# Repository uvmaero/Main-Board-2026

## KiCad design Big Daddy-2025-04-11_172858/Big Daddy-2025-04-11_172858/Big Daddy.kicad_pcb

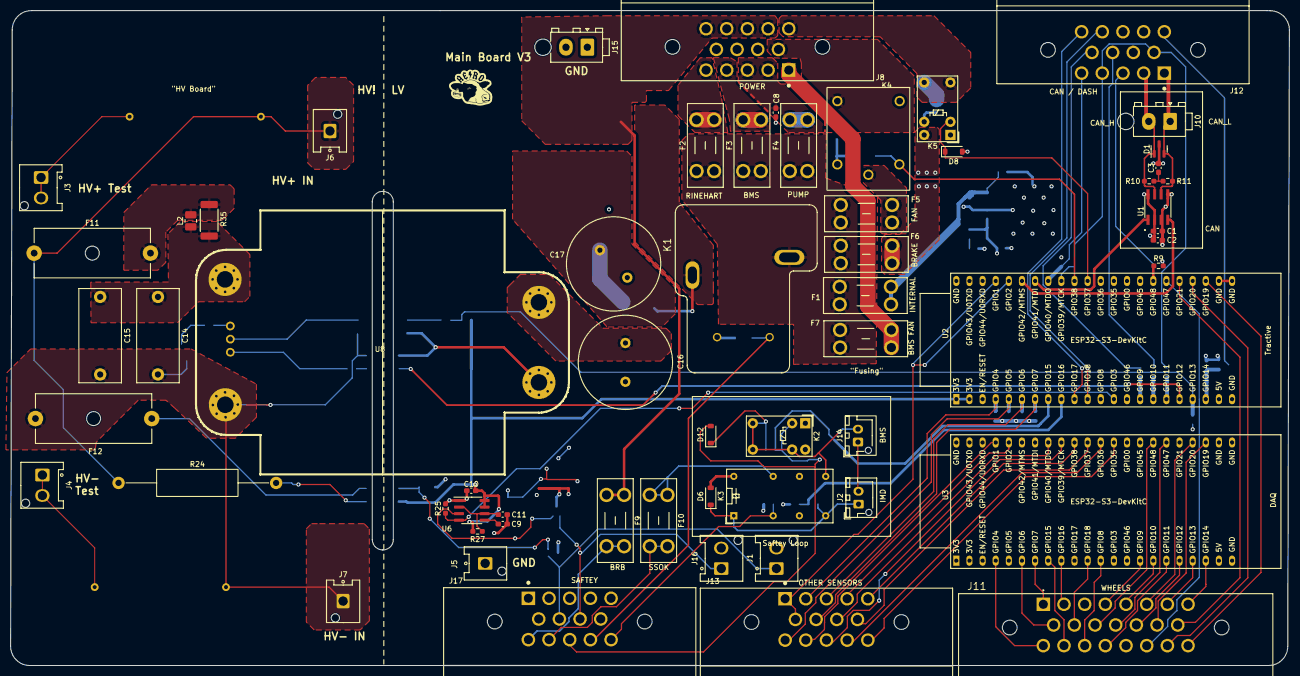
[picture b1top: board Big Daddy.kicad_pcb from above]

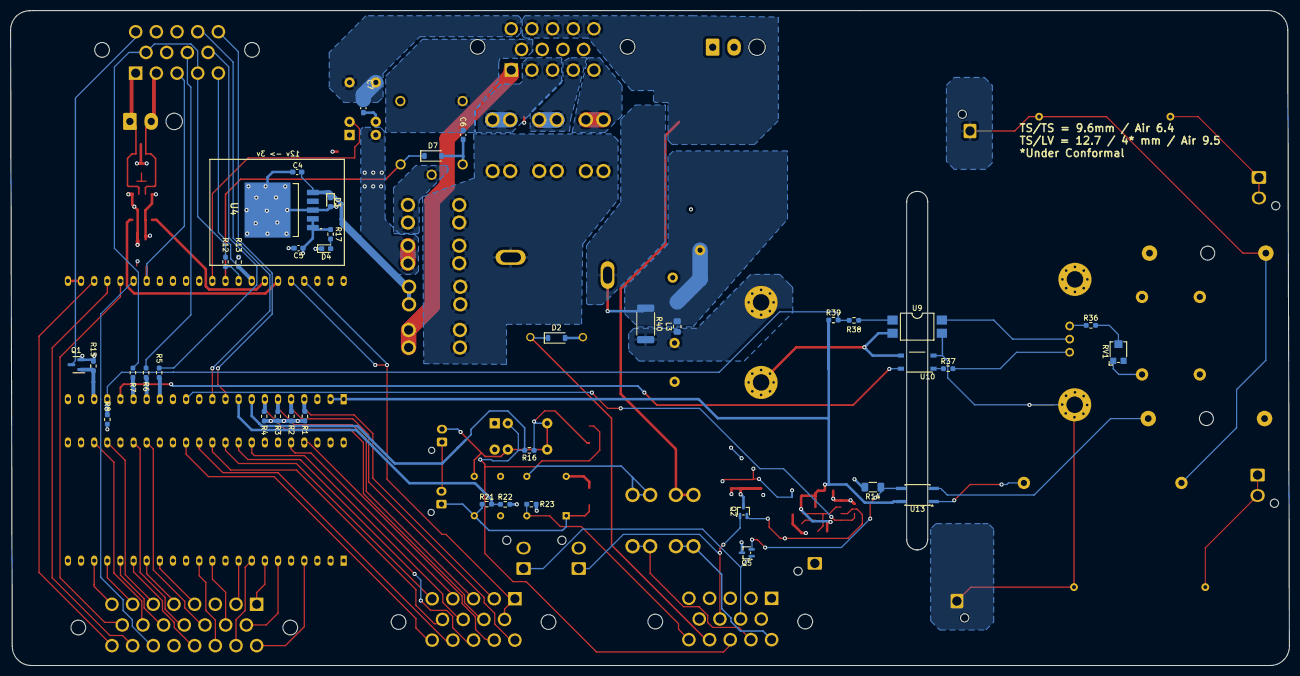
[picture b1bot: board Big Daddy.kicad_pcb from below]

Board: 4 copper layers, 247.3 x 126.6 mm, 101 parts (39 on the bottom side), 102 nets.

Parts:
C1, C2, C3, C9, C10: .1uF; C_0603_1608Metric_Pad1.08x0.95mm_HandSolder
C4, C6, C7, C8, C11: 10uF; C_0603_1608Metric_Pad1.08x0.95mm_HandSolder
C5: 22uF; C_0603_1608Metric_Pad1.08x0.95mm_HandSolder
C14, C15: 0.68uF; C_Rect_L18.0mm_W8.0mm_P15.00mm_FKS3_FKP3
C16, C17: 4700uF; C_Radial_D18.0mm_H35.5mm_P7.50mm
D1: DESD2CAN2SOQ-7; SOT-23
D2, D6, D7, D8, D12: 1N4148W; D_SOD-123
D3: TS4148C RZG; D_0603_1608Metric_Pad1.05x0.95mm_HandSolder
D4: LED; LED_0603_1608Metric_Pad1.05x0.95mm_HandSolder
F1, F4, F6, F7: 2A; Fuseholder_Blade_Mini_Keystone_3568
F2: 10A; Fuseholder_Blade_Mini_Keystone_3568
F3, F5: 5A; Fuseholder_Blade_Mini_Keystone_3568
F9, F10: 1A; Fuseholder_Blade_Mini_Keystone_3568
F11: 5A; Fuseholder_Cylinder-5x20mm_Schurter_0031_8201_Horizontal_Op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
F12: 1A; Fuseholder_Cylinder-5x20mm_Schurter_0031_8201_Horizontal_Op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
J1: TSSI_Grn I/O; Hirose_DF63R-2P-3.96DSA_1x02_P3.96mm_Vertical
J2: IMD Button; JST_XH_B2B-XH-AM_1x02_P2.50mm_Vertical
J3: HV+; Hirose_DF63R-2P-3.96DSA_1x02_P3.96mm_Vertical
J4: HV-; Hirose_DF63R-2P-3.96DSA_1x02_P3.96mm_Vertical
J5: GND; Hirose_DF63M-1P-3.96DSA_1x01_P3.96mm_Vertical
J6: HV+; Hirose_DF63M-1P-3.96DSA_1x01_P3.96mm_Vertical
J7: HV-; Hirose_DF63M-1P-3.96DSA_1x01_P3.96mm_Vertical
J8, J12, J13, J17: Conn_01x14; TE_1-776266-1_14pin_Horizontal
J10, J15: Conn_01x02; TE_MATE-N-LOK_1-770866-x_1x02_P4.14mm_Vertical
J11: Conn_01x23; TE_1-770669-1_23pin_Horizontal
J14: BMS Button; JST_XH_B2B-XH-AM_1x02_P2.50mm_Vertical
J16: TSSI_Red I/O; Hirose_DF63R-2P-3.96DSA_1x02_P3.96mm_Vertical
K1: T9VV1K15-12S; RELAY_T9VV1K15-12S
K2, K5: G5V-1; Relay_SPDT_Omron_G5V-1
K3: G5V-2; Relay_DPDT_Omron_G5V-2
K4: J107; J1071AS3VDC
L2: 1uH; L_1008_2520Metric_Pad1.43x2.20mm_HandSolder
L3: 0.15uH; L_0805_2012Metric_Pad1.15x1.40mm_HandSolder
Q1: 2N7002; SOT-23
Q2, Q5: RU1C002UN; SOT-323_SC-70
R1, R2, R3, R4, R8, R9, R13, R15, R23, R25: 10k; R_0603_1608Metric_Pad0.98x0.95mm_HandSolder
R5, R6, R7, R12, R17: 330; R_0603_1608Metric_Pad0.98x0.95mm_HandSolder
R10, R11: 60; R_0603_1608Metric_Pad0.98x0.95mm_HandSolder
R14: 2200; R_1206_3216Metric_Pad1.30x1.75mm_HandSolder
R16, R22: 2.2k; R_0603_1608Metric_Pad0.98x0.95mm_HandSolder
R21: 5.97k; R_0603_1608Metric_Pad0.98x0.95mm_HandSolder
R24: 300k; R_Axial_DIN0516_L15.5mm_D5.0mm_P30.48mm_Horizontal
R27: 24k; R_0603_1608Metric_Pad0.98x0.95mm_HandSolder
R32, R33: 20k; R_Axial_DIN0309_L9.0mm_D3.2mm_P5.08mm_Vertical
R35, R40: 1; R_2512_6332Metric_Pad1.40x3.35mm_HandSolder
R36: 300; R_0603_1608Metric_Pad0.98x0.95mm_HandSolder
R37, R38, R39: 1k; R_0603_1608Metric_Pad0.98x0.95mm_HandSolder
RV1: 50k TC33x-2-503E; Potentiometer_Bourns_TC33X_Vertical
U1: MAX33054EASA+T; SOIC127P600X175-8N
U2, U3: ESP32-S3-DevKitC
U4: LT1528CQ#PBF; LT1528CQPBF
U6: ICM7555xB; SOIC-8_3.9x4.9mm_P1.27mm
U8: Vicor_AERO; vicor-socket-no-cutouts
U9: LTV-817S; SMDIP-4_W9.53mm
U10: TLP184; MFSOP6-4_4.4x3.6mm_P1.27mm
U13: LTV-352T; SO-4_4.4x3.6mm_P2.54mm

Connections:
/Connectors/BL_SPEED: J11.23, U2.25 (GPIO19/USB_D-)
/Connectors/BL_STRAIN0: J13.11, U3.41 (GPIO1/ADC1_CH0)
/Connectors/BL_STRAIN1: J13.4, U3.40 (GPIO2/ADC1_CH1)
/Connectors/BL_SUS: J11.7, U3.19 (GPIO13/ADC2_CH2)
/Connectors/BL_TEMP: J11.8, U3.20 (GPIO14/ADC2_CH3)
/Connectors/BMS_12V: F3.2, J8.4
/Connectors/BMS_FAN_PWR_OUT: F7.2, J8.1
/Connectors/BMS_FAULT_SIG: D12.2 (A), J17.12, K2.2, R16.2, U2.8 (GPIO15/ADC2_CH4/32K_P)
/Connectors/BMS_Fault_ind: J12.8, R6.1
/Connectors/BRAKE_PWR_OUT: C7.1, J8.10, K5.5, K5.6
/Connectors/BRB_LOOP: F9.2, J17.10
/Connectors/BRB_RTN: D2.1 (K), J17.13, K1.1
/Connectors/BR_SPEED: J11.22, U2.26 (GPIO20/USB_D+)
/Connectors/BR_STRAIN0: J11.19, U3.17 (GPIO11/ADC2_CH0)
/Connectors/BR_STRAIN1: J11.13, U3.18 (GPIO12/ADC2_CH1)
/Connectors/BR_SUS: J11.4, U3.15 (GPIO9/ADC1_CH8)
/Connectors/BR_TEMP: J11.5, U3.16 (GPIO10/ADC1_CH9)
/Connectors/Batt_12_IN: F9.1, J8.11, J8.12, J8.13, J8.14
/Connectors/Brake_Regen: J12.13, U2.11 (GPIO18/ADC2_CH7)
/Connectors/CAN_H: D1.1 (K), J10.2, J12.2, R10.1, U1.7 (CANH)
/Connectors/CAN_L: D1.2 (K), J10.1, J12.1, R11.2, U1.6 (CANL)
/Connectors/Coast_Regen: J12.14, U2.10 (GPIO17/ADC2_CH6)
/Connectors/DRIVE_MODE_BTTN: J12.5, R13.1, U2.37 (GPIO40/MTDO)
/Connectors/DRIVE_MODE_LED: J12.4, J12.6, R7.1, R12.2
/Connectors/FAN_PWR_OUT: C6.1, J8.6, K4.1
/Connectors/FBrake: J13.3, R3.1, U2.6 (GPIO6/ADC1_CH5)
/Connectors/FL_SPEED: J11.15, U2.27 (GPIO21)
/Connectors/FL_STRAIN0: J11.10, U3.11 (GPIO18/ADC2_CH7)
/Connectors/FL_STRAIN1: J11.18, U3.12 (GPIO8/ADC1_CH7)
/Connectors/FL_SUS: J11.17, U3.8 (GPIO15/ADC2_CH4/32K_P)
/Connectors/FL_TEMP: J11.2, U3.9 (GPIO16/ADC2_CH5/32K_N)
/Connectors/FR_SPEED: J11.21, U2.28 (GPIO47)
/Connectors/FR_STRAIN0: J11.9, U3.6 (GPIO6/ADC1_CH5)
/Connectors/FR_STRAIN1: J11.1, U3.7 (GPIO7/ADC1_CH6)
/Connectors/FR_SUS: J11.16, U3.4 (GPIO4/ADC1_CH3)
/Connectors/FR_TEMP: J11.14, U3.25 (GPIO19/USB_D-)
/Connectors/GPS_RX: J13.12, U3.36 (GPIO39/MTCK)
/Connectors/GPS_TX: J13.8, U3.37 (GPIO40/MTDO)
/Connectors/IMD_FAULT_SIG: J17.14, K3.4, R23.1
/Connectors/IMD_Fault_ind: J12.9, R5.1
/Connectors/IMU_RX: J13.9, U3.34 (GPIO37)
/Connectors/IMU_TX: J13.5, U3.35 (GPIO38)
/Connectors/LoRa_RX: J13.14, U3.32 (GPIO35)
/Connectors/LoRa_TX: J13.13, U3.33 (GPIO36)
/Connectors/PUMP_12V: C8.1, F4.2, J8.2, J8.3
/Connectors/PUMP_TEMP_IN: J13.1, J13.6, U2.40 (GPIO2/ADC1_CH1), U2.41 (GPIO1/ADC1_CH0)
/Connectors/Pedal_0: J13.2, R1.1, U2.4 (GPIO4/ADC1_CH3)
/Connectors/Pedal_1: J13.10, R2.1, U2.5 (GPIO5/ADC1_CH4)
/Connectors/RBrake: J13.7, R4.1, U2.7 (GPIO7/ADC1_CH6)
/Connectors/RINE_12V: F2.2, J8.5
/Connectors/RPi_RX: J11.12, U3.28 (GPIO47)
/Connectors/RPi_TX: J11.11, U3.29 (GPIO48)
/Connectors/RTD_BUZZER_OUT: J12.10, Q1.3 (D)
/Connectors/START_BTTN: J12.3, R9.1, U2.29 (GPIO48)
/Connectors/STEERING: J11.6, U3.26 (GPIO20/USB_D+)
/Connectors/TSSI_Green_in: J1.1, J17.7, Q5.1 (D)
/Connectors/TSSI_Green_out: C4.1, D3.1 (K), F1.2, J1.2, J2.2, J14.1, J16.2, J17.6, J17.9, K2.10, U4.5 (VIN)
/Connectors/TSSI_Red_in: J16.1, J17.8, Q2.1 (D)
/Connectors/TSV: F10.2, J17.11
/Cooling/BRAKE_12V: F6.2, K5.10
/Cooling/Brake_SIG_Out: D8.1 (K), K5.2, U2.34 (GPIO37)
/Cooling/FAN_12V: F5.2, K4.2
/Cooling/Fan_SIG_Out: D7.1 (K), K4.C1, U2.35 (GPIO38)
/Fusing/LOOP_OUT: F10.1, K3.13
/Fusing/Vicor_In: C17.1, K1.3, L3.2, R40.1
/High Voltage/DCDC/EN_HV: U8.3 (EN), U9.4
/High Voltage/DCDC/FAULT_HV: R37.2, U8.4 (FT)
/High Voltage/DCDC/HV+: F11.2, L2.1, R35.2
/High Voltage/DCDC/HV-: C14.2, C15.2, F12.1, J7.1, R33.2, RV1.1, U8.5 (-IN), U9.3, U10.3
/High Voltage/DCDC/TRIM_HV: R36.1, U8.2 (TR)
/High Voltage/TSAL/555_OUT: Q2.2 (G), U6.3 (Q)
/High Voltage/TSAL/HV+: F11.1, J6.1, R24.1, R32.2
/High Voltage/TSAL/HV-: F12.2, U13.2
/High Voltage/TSAL/pass: C11.1, R27.2, U6.2 (TR), U6.6 (THR)
/High Voltage/TSSI_Fault: R25.1, U2.13 (GPIO3/ADC1_CH2), U6.4 (R)
/High Voltage/Vicor_Enable: R8.1, R38.1, R39.2, U2.19 (GPIO13/ADC2_CH2)
/High Voltage/Vicor_Fault: U2.18 (GPIO12/ADC2_CH1), U10.6
/Latching/BMS_Switch: D12.1 (K), J14.2, K2.5, K2.6, K2.9, K3.9, R16.1
/Latching/IMD_IND: R21.2, R22.1, U2.9 (GPIO16/ADC2_CH5/32K_N)
/Latching/IMD_SWITCH: D6.1 (K), J2.1, K3.1, K3.8, R21.1
/Microcontrolller/CAN_RX: U1.4 (RXD), U2.39 (GPIO42/MTMS)
/Microcontrolller/CAN_TX: U1.1 (TXD), U2.38 (GPIO41/MTDI)
/Microcontrolller/RTD_BUZZER: Q1.1 (G), R15.1, U2.20 (GPIO14/ADC2_CH3)
GND: C1.2, C2.2, C3.2, C4.2, C5.2, C6.2, C7.2, C8.2, C9.2, C10.2, C11.2, C16.2, C17.2, D1.3 (A), D2.2 (A), D3.2 (A), D4.1 (K), D6.2 (A), D7.2 (A), D8.2 (A), J5.1, J8.7, J8.8, J8.9, J11.3, J11.20, J12.7, J12.11, J12.12, J15.1, J15.2, K1.2, K3.16, K4.C2, K5.9, Q1.2 (S), Q2.3 (S), Q5.3 (S), R1.2, R2.2, R3.2, R4.2, R8.2, R9.2, R13.2, R14.2, R15.2, R22.2, R23.2, R25.2, U1.2 (GND), U1.8 (STBY), U2.22 (GND), U2.23 (GND), U2.24 (GND), U2.44 (GND), U3.22 (GND), U3.23 (GND), U3.24 (GND), U3.44 (GND), U4.3 (GND), U6.1 (GND), U8.8 (-OUT), U9.2, U10.4
unnamed: C3.1, R10.2, R11.1
unnamed: D4.2 (A), R17.2
unnamed: F1.1, F2.1, F3.1, F4.1, F5.1, F6.1, F7.1, K1.4
unnamed: J3.1, J3.2, R32.1
unnamed: J4.1, J4.2, R33.1
unnamed: Q5.2 (G), R14.1, U13.3
unnamed: R24.2, U13.1
unnamed: R36.2, RV1.2
unnamed: R37.1, U10.1
unnamed: R38.2, U9.1
unnamed: R5.2, U2.15 (GPIO9/ADC1_CH8)
unnamed: R6.2, U2.16 (GPIO10/ADC1_CH9)
unnamed: R7.2, U2.17 (GPIO11/ADC2_CH0)
unnamed: R12.1, U2.36 (GPIO39/MTCK)
unnamed: C9.1, U6.5 (CV)
unnamed: C14.1, C15.1, L2.2, R35.1, U8.1 (+IN)
unnamed: C16.1, L3.1, R40.2, U8.9 (+OUT)
VDD: C1.1, C2.1, C5.1, C10.1, R17.1, R27.1, R39.1, U1.3 (VDD), U1.5 (VL), U2.1 (3V3), U2.2 (3V3), U3.1 (3V3), U3.2 (3V3), U4.1 (OUTPUT), U4.2 (SENSE), U6.7 (DIS), U6.8 (VCC), U13.4

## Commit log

2026-03-17 cut out diode arrays
2026-03-25 updated lights
2026-03-25 footprints found for fets and Rs
2026-03-26 Rerouted PCB
2026-03-26 BOM update
2026-03-31 Deleted TSV schematic
